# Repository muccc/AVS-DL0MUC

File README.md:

Moved permanently to https://github.com/dl0muc/avs_operation_center

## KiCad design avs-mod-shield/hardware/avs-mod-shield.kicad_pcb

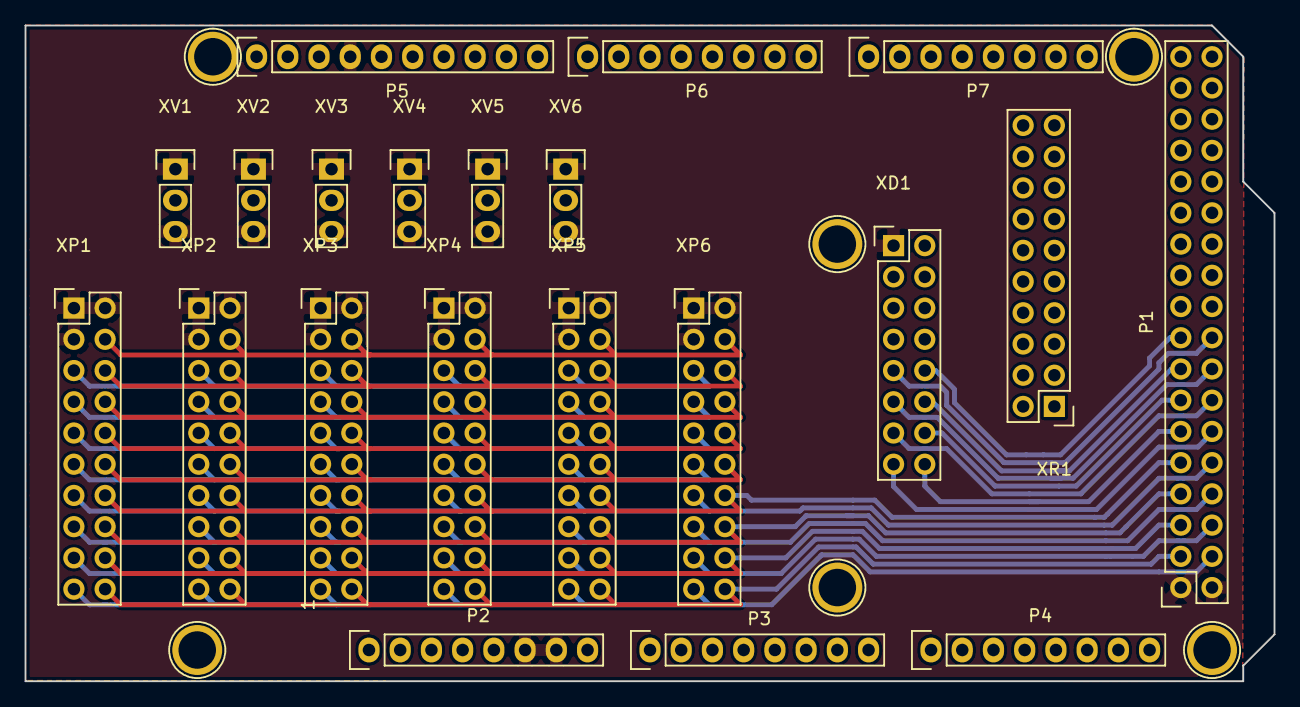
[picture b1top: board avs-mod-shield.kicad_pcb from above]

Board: 2 copper layers, 101.6 x 53.3 mm, 27 parts (0 on the bottom side), 19 nets.

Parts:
P1: Digital; Socket_Strip_Arduino_2x18
P2: Power; Socket_Strip_Arduino_1x08
P3, P4: Analog; Socket_Strip_Arduino_1x08
P5: PWM; Socket_Strip_Arduino_1x10
P6: PWM; Socket_Strip_Arduino_1x08
P7: Communication; Socket_Strip_Arduino_1x08
P8, P9, P10, P11, P12, P13: CONN_1; Arduino_1pin
XD1: CONN_02X08; Pin_Header_Straight_2x08
XP1, XP2, XP3, XP4, XP5, XP6: CONN_02X10; Pin_Header_Straight_2x10
XR1: CONN_02X10; Pin_Header_Straight_2x10
XV1, XV2, XV3, XV4, XV5, XV6: CONN_01X03; Pin_Header_Straight_1x03

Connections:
+5V: P1.35, P1.36, P2.5, XD1.2, XV1.2, XV2.2, XV3.2, XV4.2, XV5.2, XV6.2
//G: XP1.4, XP2.4, XP3.4, XP4.4, XP5.4, XP6.4
/AP0: P1.3, XP1.20, XP2.20, XP3.20, XP4.20, XP5.20, XP6.20
/AP1: P1.4, XP1.19, XP2.19, XP3.19, XP4.19, XP5.19, XP6.19
/AP2: P1.5, XP1.18, XP2.18, XP3.18, XP4.18, XP5.18, XP6.18
/AP3: P1.6, XP1.17, XP2.17, XP3.17, XP4.17, XP5.17, XP6.17
/AP4: P1.7, XP1.16, XP2.16, XP3.16, XP4.16, XP5.16, XP6.16
/AP5: P1.8, XP1.15, XP2.15, XP3.15, XP4.15, XP5.15, XP6.15
/AP6: P1.9, XP1.14, XP2.14, XP3.14, XP4.14, XP5.14, XP6.14
/AP7: P1.10, XP1.13, XP2.13, XP3.13, XP4.13, XP5.13, XP6.13
/P0: P1.11, XD1.16, XP1.12, XP2.12, XP3.12, XP4.12, XP5.12, XP6.12
/P1: P1.12, XD1.15, XP1.11, XP2.11, XP3.11, XP4.11, XP5.11, XP6.11
/P2: P1.13, XD1.14, XP1.10, XP2.10, XP3.10, XP4.10, XP5.10, XP6.10
/P3: P1.14, XD1.13, XP1.9, XP2.9, XP3.9, XP4.9, XP5.9, XP6.9
/P4: P1.15, XD1.12, XP1.8, XP2.8, XP3.8, XP4.8, XP5.8, XP6.8
/P5: P1.16, XD1.11, XP1.7, XP2.7, XP3.7, XP4.7, XP5.7, XP6.7
/P6: P1.17, XD1.10, XP1.6, XP2.6, XP3.6, XP4.6, XP5.6, XP6.6
/P7: P1.18, XD1.9, XP1.5, XP2.5, XP3.5, XP4.5, XP5.5, XP6.5
GND: P1.1, P1.2, P2.6, P2.7, P5.4, XD1.1, XP1.1, XP1.2, XP1.3, XP2.1, XP2.2, XP2.3, XP3.1, XP3.2, XP3.3, XP4.1, XP4.2, XP4.3, XP5.1, XP5.2, XP5.3, XP6.1, XP6.2, XP6.3, XV1.1, XV1.3, XV2.1, XV2.3, XV3.1, XV3.3, XV4.1, XV4.3, XV5.1, XV5.3, XV6.1, XV6.3

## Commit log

2016-02-08 Erste Datenblätter und Denkanstoesse
2016-02-09 Added AVS-1280 Arduino Shield
2016-02-09 Added avs-audio-matrix
2016-02-09 renamed folder
2016-02-09 continued avs-mod-shield
2016-02-11 Erstes Controller Zeugs
2016-08-05 Moved file to correct folder
2016-08-05 Moved permanently to https://github.com/dl0muc/avs_operation_center
